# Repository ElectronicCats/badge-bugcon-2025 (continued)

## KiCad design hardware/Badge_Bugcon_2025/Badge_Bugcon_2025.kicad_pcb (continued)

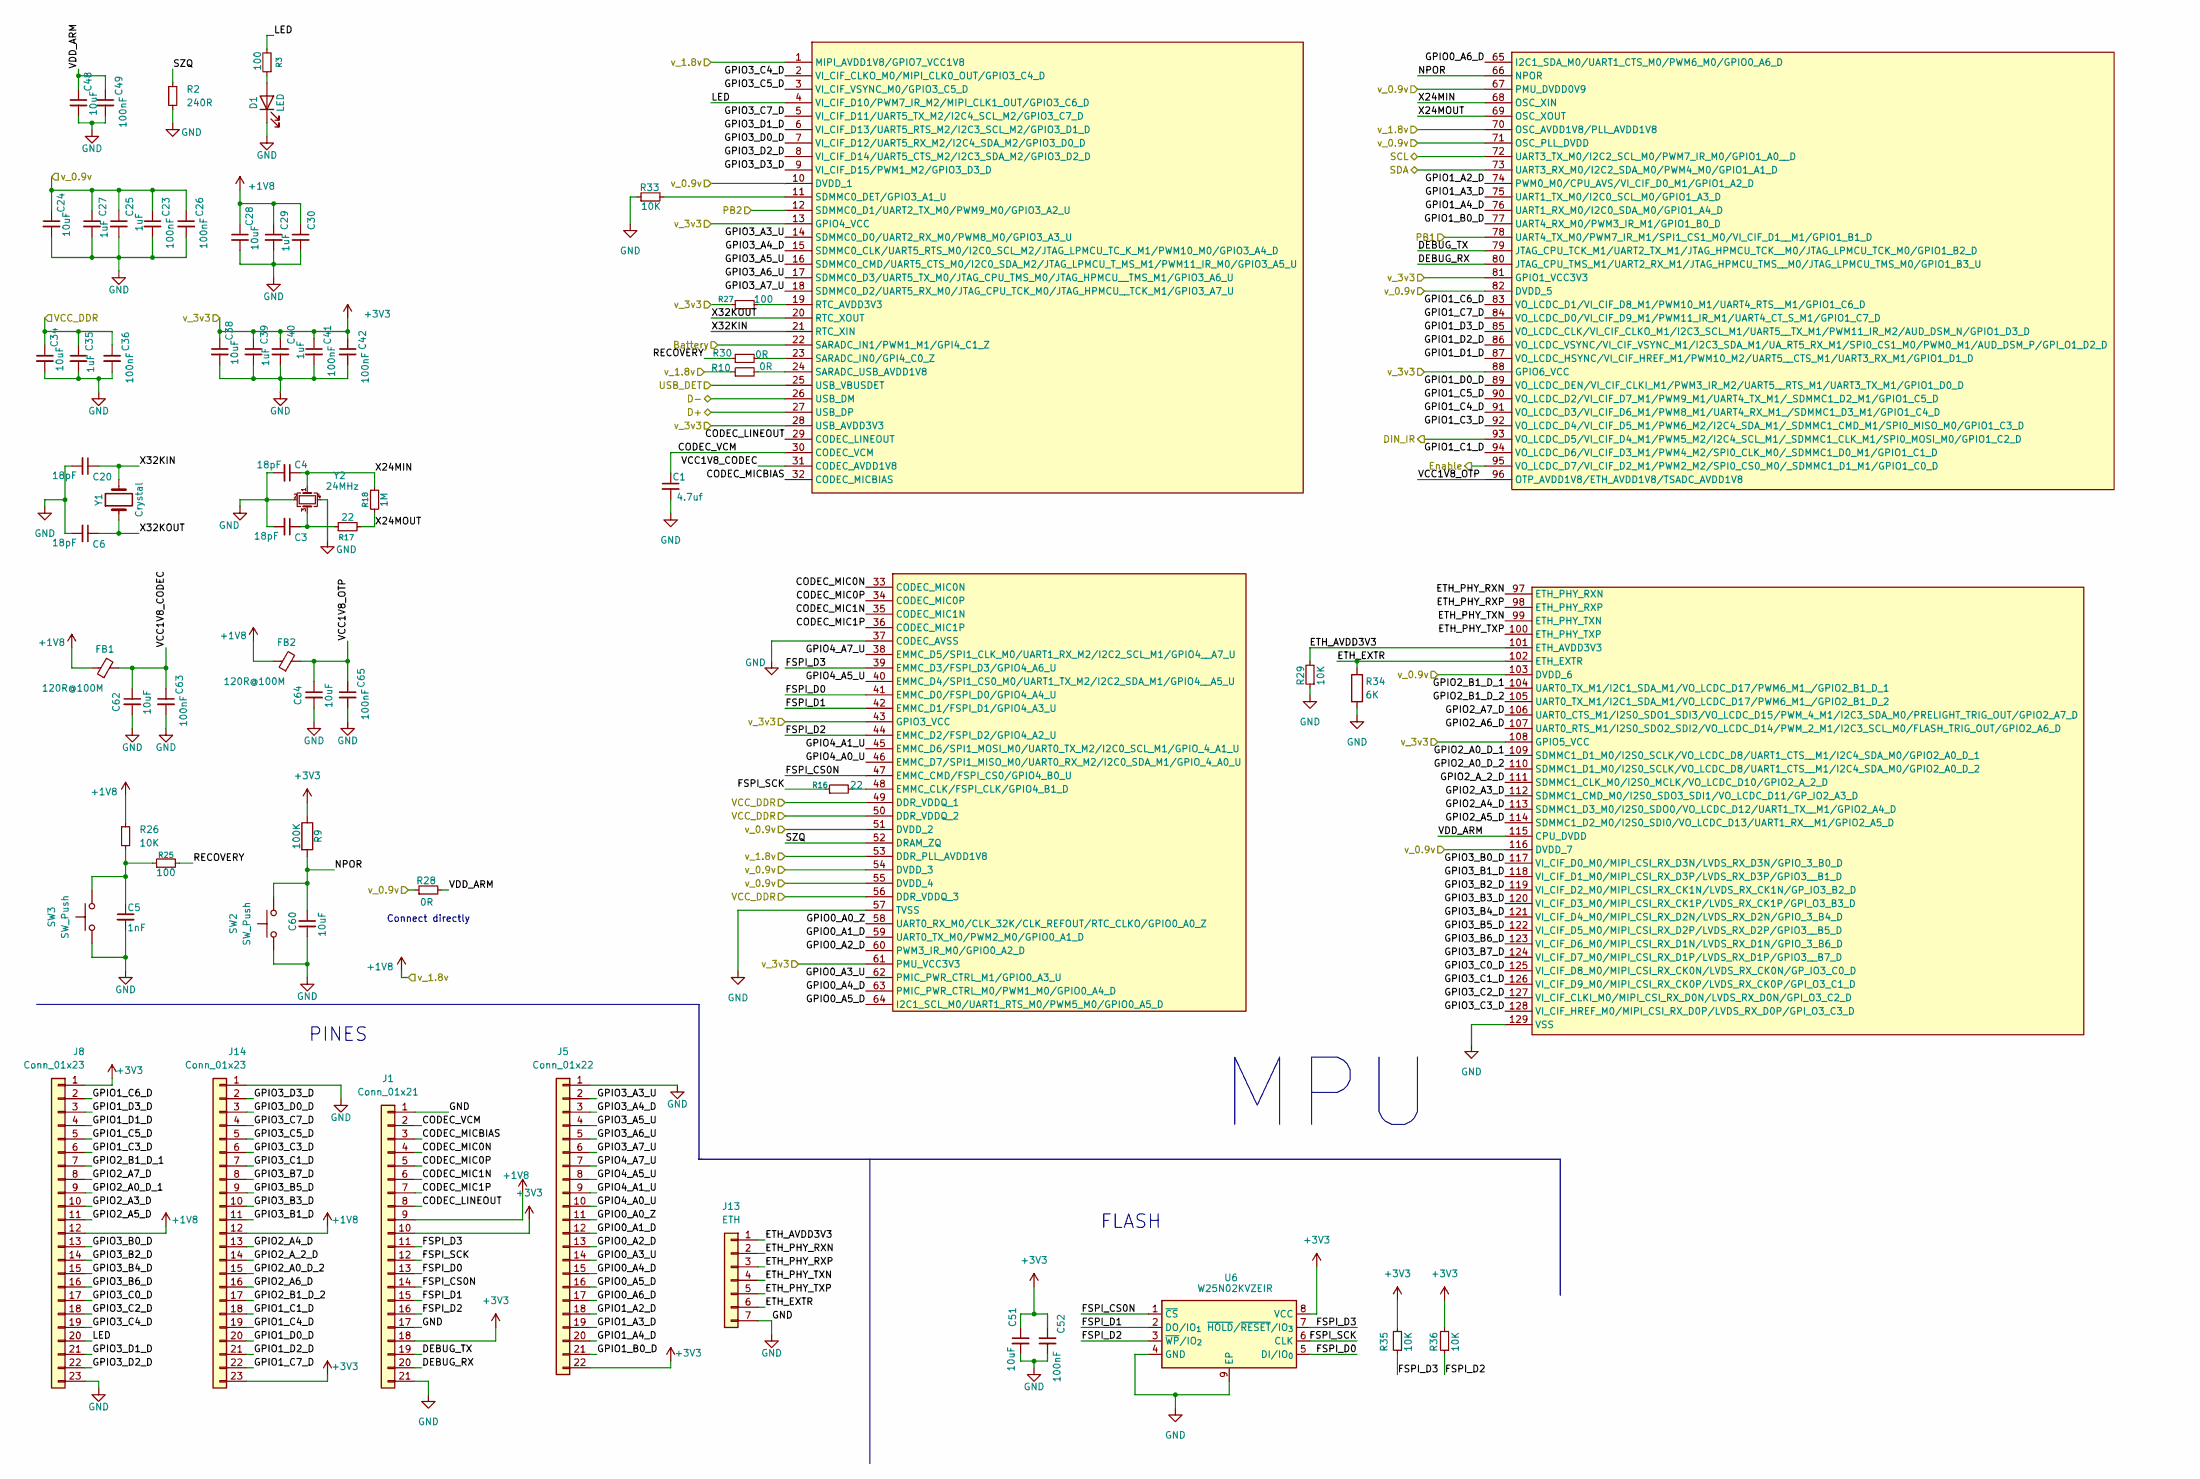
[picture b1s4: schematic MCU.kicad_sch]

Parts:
C1: 4.7uf; C_0402_1005Metric; LCSC# C6119795
C3, C4, C6, C20: 18pF; C_0402_1005Metric; LCSC# C161534
C5: 1nF; C_0402_1005Metric; LCSC# C189467
C23, C26, C36, C41, C42, C49, C52, C63, C65: 100nF; C_0402_1005Metric; LCSC# C77020
C24, C28, C34, C38, C48, C51, C62, C64: 10uF; C_0402_1005Metric; LCSC# C7472949
C25, C27, C29, C30, C35, C39, C40: 1uF; C_0402_1005Metric; LCSC# C52923
C60: 10uF; C_0603_1608Metric; LCSC# C96446
D1: LED; LED_0603_1608Metric; LCSC# C375573
FB1, FB2: 120R@100M; L_0603_1608Metric; LCSC# C14709
J1: Conn_01x21; PinHeader_1x21_P2.54mm_Vertical
J5: Conn_01x22; PinHeader_1x22_P2.54mm_Vertical
J8, J14: Conn_01x23; PinHeader_1x23_P2.54mm_Vertical
J13: ETH; PinHeader_1x07_P2.54mm_Vertical
R2: 240R; R_0402_1005Metric; LCSC# C25094
R3, R25, R27: 100; R_0402_1005Metric; LCSC# C2906860
R9: 100K; R_0402_1005Metric; LCSC# C844674
R10, R28, R30: 0R; R_0402_1005Metric; LCSC# C106231
R16, R17: 22; R_0402_1005Metric; LCSC# C159964
R18: 1M; R_0402_1005Metric; LCSC# C131492
R26, R29, R33, R35, R36: 10K; R_0402_1005Metric; LCSC# C2759535
R34: 6K; R_0805_2012Metric; LCSC# C2828725
SW2, SW3: SW_Push; TS1088R02026; LCSC# C455281
U6: W25N02KVZEIR; WSON-8-1EP_8x6mm_P1.27mm_EP3.4x4.3mm; LCSC# C3010298
U8: RV1106G3; LCSC# C5328706
Y1: Crystal; Crystal_SMD_3215-2Pin_3.2x1.5mm; LCSC# C620155
Y2: 24MHz; Crystal_SMD_3225-4Pin_3.2x2.5mm; LCSC# C70590

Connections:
+1V8: C28.1, C29.1, C30.1, FB1.1, FB2.1, J1.9, J8.12, J14.12, R10.1, R26.1, U8.1 (MIPI_AVDD1V8/GPIO7_VCC1V8), U8.53 (DDR_PLL_AVDD1V8), U8.70 (OSC_AVDD1V8/PLL_AVDD1V8); also elsewhere on the board
+3V3: C38.1, C39.1, C40.1, C41.1, C42.1, C51.1, C52.1, J1.10, J1.18, J5.22, J8.1, J14.23, R9.1, R27.1, R35.2, R36.2, U6.8 (VCC), U8.13 (GPIO4_VCC), U8.28 (USB_AVDD3V3), U8.43 (GPIO3_VCC), U8.61 (PMU_VCC3V3), U8.81 (GPIO1_VCC3V3), U8.88 (GPIO6_VCC), U8.108 (GPIO5_VCC); also elsewhere on the board
/Buck_Converter/VCC_DDR: C34.1, C35.1, C36.1, U8.49 (DDR_VDDQ_1), U8.50 (DDR_VDDQ_2), U8.56 (DDR_VDDQ_3); also elsewhere on the board
/Buck_Converter/v_0.9v: C23.1, C24.1, C25.1, C26.1, C27.1, R28.1, U8.10 (DVDD_1), U8.51 (DVDD_2), U8.54 (DVDD_3), U8.55 (DVDD_4), U8.67 (PMU_DVDD0V9), U8.71 (OSC_PLL_DVDD), U8.82 (DVDD_5), U8.103 (DVDD_6), U8.116 (DVDD_7); also elsewhere on the board
/MCU/Battery: U8.22 (SARADC_IN1/PWM1_M1/GPI4_C1_Z); also elsewhere on the board
/MCU/CODEC_LINEOUT: J1.8, U8.29 (CODEC_LINEOUT)
/MCU/CODEC_MIC0N: J1.4, U8.33 (CODEC_MIC0N)
/MCU/CODEC_MIC0P: J1.5, U8.34 (CODEC_MIC0P)
/MCU/CODEC_MIC1N: J1.6, U8.35 (CODEC_MIC1N)
/MCU/CODEC_MIC1P: J1.7, U8.36 (CODEC_MIC1P)
/MCU/CODEC_MICBIAS: J1.3, U8.32 (CODEC_MICBIAS)
/MCU/CODEC_VCM: C1.1, J1.2, U8.30 (CODEC_VCM)
/MCU/D+: U8.27 (USB_DP); also elsewhere on the board
/MCU/D-: U8.26 (USB_DM); also elsewhere on the board
/MCU/DEBUG_RX: J1.20, U8.80 (JTAG_CPU_TMS_M1/UART2_RX_M1/JTAG_HPMCU_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)
/MCU/DEBUG_TX: J1.19, U8.79 (JTAG_CPU_TCK_M1/UART2_TX_M1/JTAG_HPMCU_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)
/MCU/DIN_IR: U8.93 (VO_LCDC_D5/VI_CIF_D4_M1/PWM5_M2/I2C4_SC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); also elsewhere on the board
/MCU/ETH_AVDD3V3: J13.1, R29.2, U8.101 (ETH_AVDD3V3)
/MCU/ETH_EXTR: J13.6, R34.1, U8.102 (ETH_EXTR)
/MCU/ETH_PHY_RXN: J13.2, U8.97 (ETH_PHY_RXN)
/MCU/ETH_PHY_RXP: J13.3, U8.98 (ETH_PHY_RXP)
/MCU/ETH_PHY_TXN: J13.4, U8.99 (ETH_PHY_TXN)
/MCU/ETH_PHY_TXP: J13.5, U8.100 (ETH_PHY_TXP)
/MCU/Enable: U8.95 (VO_LCDC_D7/VI_CIF_D2_M1/PWM2_M2/SPI0_CS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); also elsewhere on the board
/MCU/FSPI_CS0N: J1.14, U6.1 (~CS), U8.47 (EMMC_CMD/FSPI_CS0/GPIO4_B0_U)
/MCU/FSPI_D0: J1.13, U6.5 (DI/IO_{0}), U8.41 (EMMC_D0/FSPI_D0/GPIO4_A4_U)
/MCU/FSPI_D1: J1.15, U6.2 (DO/IO_{1}), U8.42 (EMMC_D1/FSPI_D1/GPIO4_A3_U)
/MCU/FSPI_D2: J1.16, R36.1, U6.3 (~WP/IO_{2}), U8.44 (EMMC_D2/FSPI_D2/GPIO4_A2_U)
/MCU/FSPI_D3: J1.11, R35.1, U6.7 (~HOLD/~RESET/IO_{3}), U8.39 (EMMC_D3/FSPI_D3/GPIO4_A6_U)
/MCU/FSPI_SCK: J1.12, R16.1, U6.6 (CLK)
/MCU/GPIO0_A0_Z: J5.11, U8.58 (UART0_RX_M0/CLK_32K/CLK_REFOUT/RTC_CLKO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)
/MCU/GPIO0_A1_D: J5.12, U8.59 (UART0_TX_M0/PWM2_M0/GPIO0_A1_D)
/MCU/GPIO0_A2_D: J5.13, U8.60 (PWM3_IR_M0/GPIO0_A2_D)
/MCU/GPIO0_A3_U: J5.14, U8.62 (PMIC_PWR_CTRL_M1/GPIO0_A3_U)
/MCU/GPIO0_A4_D: J5.15, U8.63 (PMIC_PWR_CTRL_M0/PWM1_M0/GPIO0_A4_D)
/MCU/GPIO0_A5_D: J5.16, U8.64 (I2C1_SCL_M0/UART1_RTS_M0/PWM5_M0/GPIO0_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)
/MCU/GPIO0_A6_D: J5.17, U8.65 (I2C1_SDA_M0/UART1_CTS_M0/PWM6_M0/GPIO0_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)
/MCU/GPIO1_A2_D: J5.18, U8.74 (PWM0_M0/CPU_AVS/VI_CIF_D0_M1/GPIO1_A2_D)
/MCU/GPIO1_A3_D: J5.19, U8.75 (UART1_TX_M0/I2C0_SCL_M0/GPIO1_A3_D)
/MCU/GPIO1_A4_D: J5.20, U8.76 (UART1_RX_M0/I2C0_SDA_M0/GPIO1_A4_D)
/MCU/GPIO1_B0_D: J5.21, U8.77 (UART4_RX_M0/PWM3_IR_M1/GPIO1_B0_D)
/MCU/GPIO1_C1_D: J14.18, U8.94 (VO_LCDC_D6/VI_CIF_D3_M1/PWM4_M2/SPI0_CL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)
/MCU/GPIO1_C3_D: J8.6, U8.92 (VO_LCDC_D4/VI_CIF_D5_M1/PWM6_M2/I2C4_SD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)
/MCU/GPIO1_C4_D: J14.19, U8.91 (VO_LCDC_D3/VI_CIF_D6_M1/PWM8_M1/UART4_R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)
/MCU/GPIO1_C5_D: J8.5, U8.90 (VO_LCDC_D2/VI_CIF_D7_M1/PWM9_M1/UART4_T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)
/MCU/GPIO1_C6_D: J8.2, U8.83 (VO_LCDC_D1/VI_CIF_D8_M1/PWM10_M1/UART4_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)
/MCU/GPIO1_C7_D: J14.22, U8.84 (VO_LCDC_D0/VI_CIF_D9_M1/PWM11_IR_M1/UAR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)
/MCU/GPIO1_D0_D: J14.20, U8.89 (VO_LCDC_DEN/VI_CIF_CLKI_M1/PWM3_IR_M2/U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)
/MCU/GPIO1_D1_D: J8.4, U8.87 (VO_LCDC_HSYNC/VI_CIF_HREF_M1/PWM10_M2/U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)
/MCU/GPIO1_D2_D: J14.21, U8.86 (VO_LCDC_VSYNC/VI_CIF_VSYNC_M1/I2C3_SDA_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)
/MCU/GPIO1_D3_D: J8.3, U8.85 (VO_LCDC_CLK/VI_CIF_CLKO_M1/I2C3_SCL_M1/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)
/MCU/GPIO2_A0_D_1: J8.9, U8.109 (SDMMC1_D1_M0/I2S0_SCLK/VO_LCDC_D8/UART1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)
/MCU/GPIO2_A0_D_2: J14.15, U8.110 (SDMMC1_D1_M0/I2S0_SCLK/VO_LCDC_D8/UART1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)
/MCU/GPIO2_A3_D: J8.10, U8.112 (SDMMC1_CMD_M0/I2S0_SDO3_SDI1/VO_LCDC_D1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)
/MCU/GPIO2_A4_D: J14.13, U8.113 (SDMMC1_D3_M0/I2S0_SDO0/VO_LCDC_D12/UART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)
/MCU/GPIO2_A5_D: J8.11, U8.114 (SDMMC1_D2_M0/I2S0_SDI0/VO_LCDC_D13/UART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)
/MCU/GPIO2_A6_D: J14.16, U8.107 (UART0_RTS_M1/I2S0_SDO2_SDI2/VO_LCDC_D14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)
/MCU/GPIO2_A7_D: J8.8, U8.106 (UART0_CTS_M1/I2S0_SDO1_SDI3/VO_LCDC_D15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)
/MCU/GPIO2_A_2_D: J14.14, U8.111 (SDMMC1_CLK_M0/I2S0_MCLK/VO_LCDC_D10/GPI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)
/MCU/GPIO2_B1_D_1: J8.7, U8.104 (UART0_TX_M1/I2C1_SDA_M1/VO_LCDC_D17/PWM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)
/MCU/GPIO2_B1_D_2: J14.17, U8.105 (UART0_TX_M1/I2C1_SDA_M1/VO_LCDC_D17/PWM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)
/MCU/GPIO3_A3_U: J5.2, U8.14 (SDMMC0_D0/UART2_RX_M0/PWM8_M0/GPIO3_A3_U)
/MCU/GPIO3_A4_D: J5.3, U8.15 (SDMMC0_CLK/UART5_RTS_M0/I2C0_SCL_M2/JTA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)
/MCU/GPIO3_A5_U: J5.4, U8.16 (SDMMC0_CMD/UART5_CTS_M0/I2C0_SDA_M2/JTA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)
/MCU/GPIO3_A6_U: J5.5, U8.17 (SDMMC0_D3/UART5_TX_M0/JTAG_CPU_TMS_M0/J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)
/MCU/GPIO3_A7_U: J5.6, U8.18 (SDMMC0_D2/UART5_RX_M0/JTAG_CPU_TCK_M0/J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)
/MCU/GPIO3_B0_D: J8.13, U8.117 (VI_CIF_D0_M0/MIPI_CSI_RX_D3N/LVDS_RX_D3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)
/MCU/GPIO3_B1_D: J14.11, U8.118 (VI_CIF_D1_M0/MIPI_CSI_RX_D3P/LVDS_RX_D3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)
/MCU/GPIO3_B2_D: J8.14, U8.119 (VI_CIF_D2_M0/MIPI_CSI_RX_CK1N/LVDS_RX_C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)
/MCU/GPIO3_B3_D: J14.10, U8.120 (VI_CIF_D3_M0/MIPI_CSI_RX_CK1P/LVDS_RX_C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)
/MCU/GPIO3_B4_D: J8.15, U8.121 (VI_CIF_D4_M0/MIPI_CSI_RX_D2N/LVDS_RX_D2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)
/MCU/GPIO3_B5_D: J14.9, U8.122 (VI_CIF_D5_M0/MIPI_CSI_RX_D2P/LVDS_RX_D2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)
/MCU/GPIO3_B6_D: J8.16, U8.123 (VI_CIF_D6_M0/MIPI_CSI_RX_D1N/LVDS_RX_D1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)
/MCU/GPIO3_B7_D: J14.8, U8.124 (VI_CIF_D7_M0/MIPI_CSI_RX_D1P/LVDS_RX_D1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)
/MCU/GPIO3_C0_D: J8.17, U8.125 (VI_CIF_D8_M0/MIPI_CSI_RX_CK0N/LVDS_RX_C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)
/MCU/GPIO3_C1_D: J14.7, U8.126 (VI_CIF_D9_M0/MIPI_CSI_RX_CK0P/LVDS_RX_C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)
/MCU/GPIO3_C2_D: J8.18, U8.127 (VI_CIF_CLKI_M0/MIPI_CSI_RX_D0N/LVDS_RX_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)
/MCU/GPIO3_C3_D: J14.6, U8.128 (VI_CIF_HREF_M0/MIPI_CSI_RX_D0P/LVDS_RX_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)
/MCU/GPIO3_C4_D: J8.19, U8.2 (VI_CIF_CLKO_M0/MIPI_CLK0_OUT/GPIO3_C4_D)
/MCU/GPIO3_C5_D: J14.5, U8.3 (VI_CIF_VSYNC_M0/GPIO3_C5_D)
/MCU/GPIO3_C7_D: J14.4, U8.5 (VI_CIF_D11/UART5_TX_M2/I2C4_SCL_M2/GPIO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)
/MCU/GPIO3_D0_D: J14.3, U8.7 (VI_CIF_D12/UART5_RX_M2/I2C4_SDA_M2/GPIO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)
/MCU/GPIO3_D1_D: J8.21, U8.6 (VI_CIF_D13/UART5_RTS_M2/I2C3_SCL_M2/GPI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)
/MCU/GPIO3_D2_D: J8.22, U8.8 (VI_CIF_D14/UART5_CTS_M2/I2C3_SDA_M2/GPI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)
/MCU/GPIO3_D3_D: J14.2, U8.9 (VI_CIF_D15/PWM1_M2/GPIO3_D3_D)
/MCU/GPIO4_A0_U: J5.10, U8.46 (EMMC_D7/SPI1_MISO_M0/UART0_RX_M2/I2C0_S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)
/MCU/GPIO4_A1_U: J5.9, U8.45 (EMMC_D6/SPI1_MOSI_M0/UART0_TX_M2/I2C0_S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)
/MCU/GPIO4_A5_U: J5.8, U8.40 (EMMC_D4/SPI1_CS0_M0/UART1_TX_M2/I2C2_SD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)
/MCU/GPIO4_A7_U: J5.7, U8.38 (EMMC_D5/SPI1_CLK_M0/UART1_RX_M2/I2C2_SC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)
/MCU/LED: J8.20, R3.2, U8.4 (VI_CIF_D10/PWM7_IR_M2/MIPI_CLK1_OUT/GPI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)
/MCU/NPOR: C60.1, R9.2, SW2.2, U8.66 (NPOR)
/MCU/PB1: U8.78 (UART4_TX_M0/PWM7_IR_M1/SPI1_CS1_M0/VI_C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); also elsewhere on the board
/MCU/PB2: U8.12 (SDMMC0_D1/UART2_TX_M0/PWM9_M0/GPIO3_A2_U); also elsewhere on the board
/MCU/RECOVERY: R25.2, R30.1
/MCU/SCL: U8.72 (UART3_TX_M0/I2C2_SCL_M0/PWM7_IR_M0/GPIO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); also elsewhere on the board
/MCU/SDA: U8.73 (UART3_RX_M0/I2C2_SDA_M0/PWM4_M0/GPIO1_A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); also elsewhere on the board
/MCU/SZQ: R2.1, U8.52 (DRAM_ZQ)
/MCU/USB_DET: U8.25 (USB_VBUSDET); also elsewhere on the board
/MCU/VCC1V8_CODEC: C62.1, C63.1, FB1.2, U8.31 (CODEC_AVDD1V8)
/MCU/VCC1V8_OTP: C64.1, C65.1, FB2.2, U8.96 (OTP_AVDD1V8/ETH_AVDD1V8/TSADC_AVDD1V8)
/MCU/VDD_ARM: C48.1, C49.1, R28.2, U8.115 (CPU_DVDD)
/MCU/X24MIN: C4.1, R18.1, U8.68 (OSC_XIN), Y2.1
/MCU/X24MOUT: R17.2, R18.2, U8.69 (OSC_XOUT)
/MCU/X32KIN: C20.1, U8.21 (RTC_XIN), Y1.2
/MCU/X32KOUT: C6.1, U8.20 (RTC_XOUT), Y1.1
GND: C1.2, C3.2, C4.2, C5.2, C6.2, C20.2, C23.2, C24.2, C25.2, C26.2, C27.2, C28.2, C29.2, C30.2, C34.2, C35.2, C36.2, C38.2, C39.2, C40.2, C41.2, C42.2, C48.2, C49.2, C51.2, C52.2, C60.2, C62.2, C63.2, C64.2, C65.2, D1.1 (K), J1.1, J1.17, J1.21, J5.1, J8.23, J13.7, J14.1, R2.2, R29.1, R33.1, R34.2, SW2.1, SW3.1, U6.4 (GND), U6.9 (EP), U8.37 (CODEC_AVSS), U8.57 (TVSS), U8.129 (VSS), Y2.2, Y2.4; also elsewhere on the board
unnamed: C3.1, R17.1, Y2.3
unnamed: C5.1, R25.1, R26.2, SW3.2
unnamed: D1.2 (A), R3.1
unnamed: R27.2, U8.19 (RTC_AVDD3V3)
unnamed: R30.2, U8.23 (SARADC_IN0/GPI4_C0_Z)
unnamed: R10.2, U8.24 (SARADC_USB_AVDD1V8)
unnamed: R33.2, U8.11 (SDMMC0_DET/GPIO3_A1_U)
unnamed: R16.2, U8.48 (EMMC_CLK/FSPI_CLK/GPIO4_B1_D)

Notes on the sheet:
MPU
Connect directly
PINES
FLASH

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
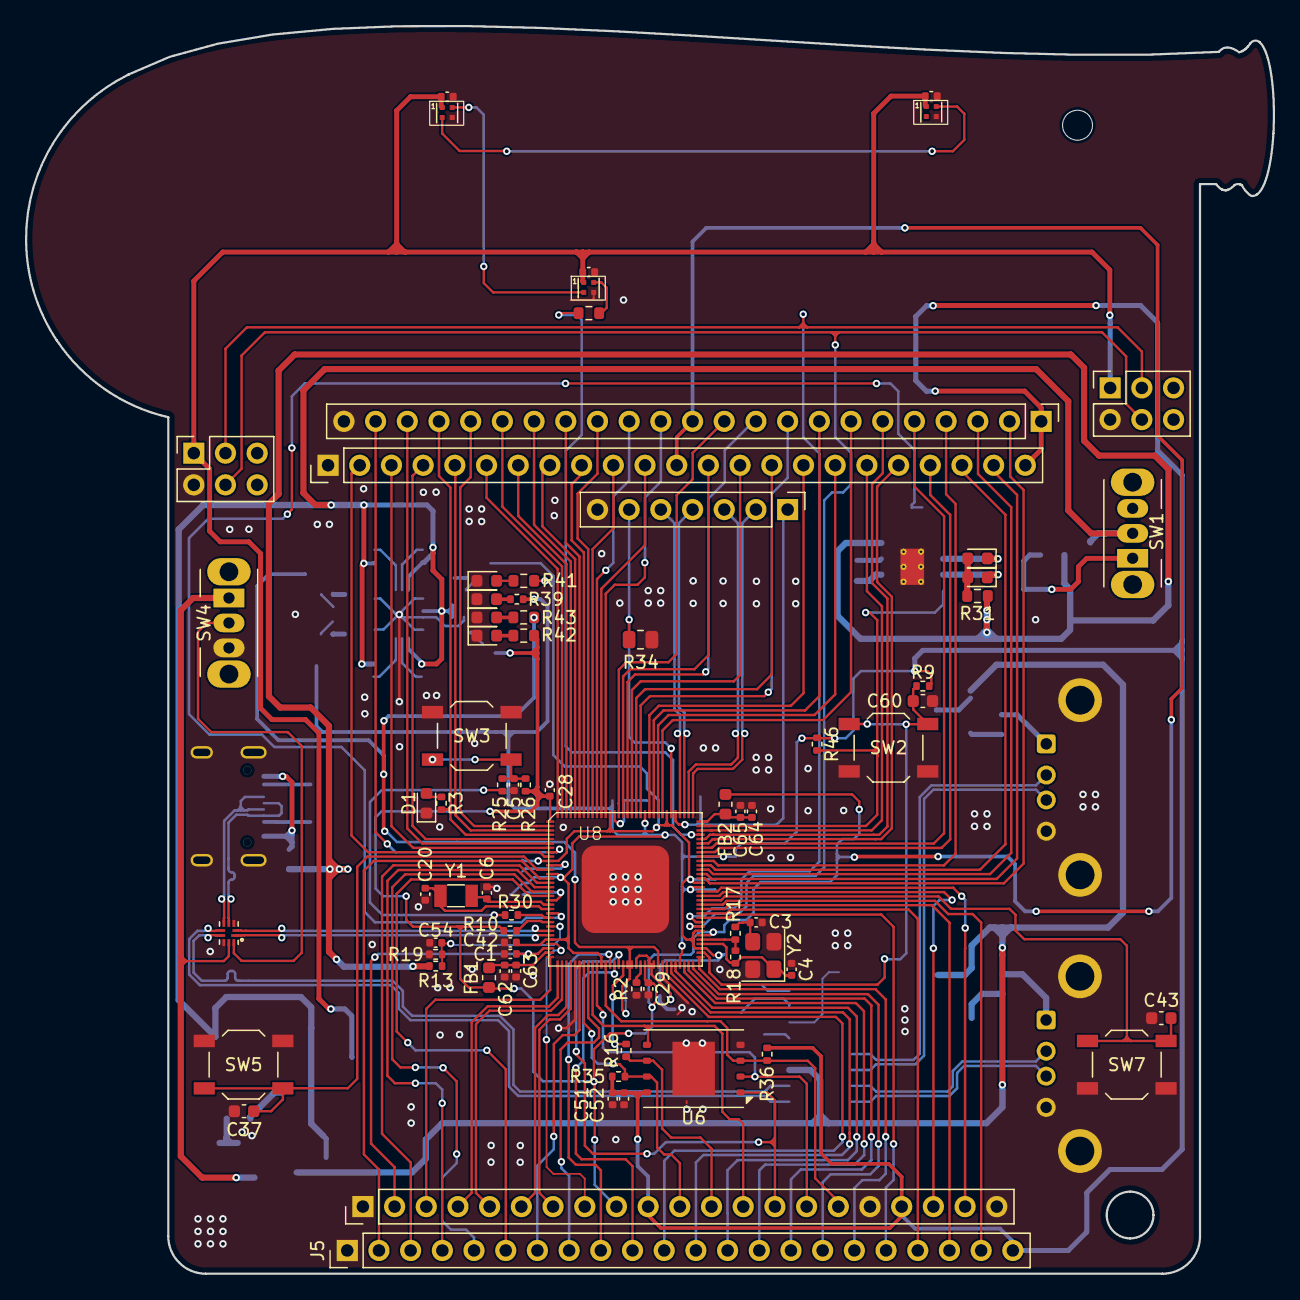
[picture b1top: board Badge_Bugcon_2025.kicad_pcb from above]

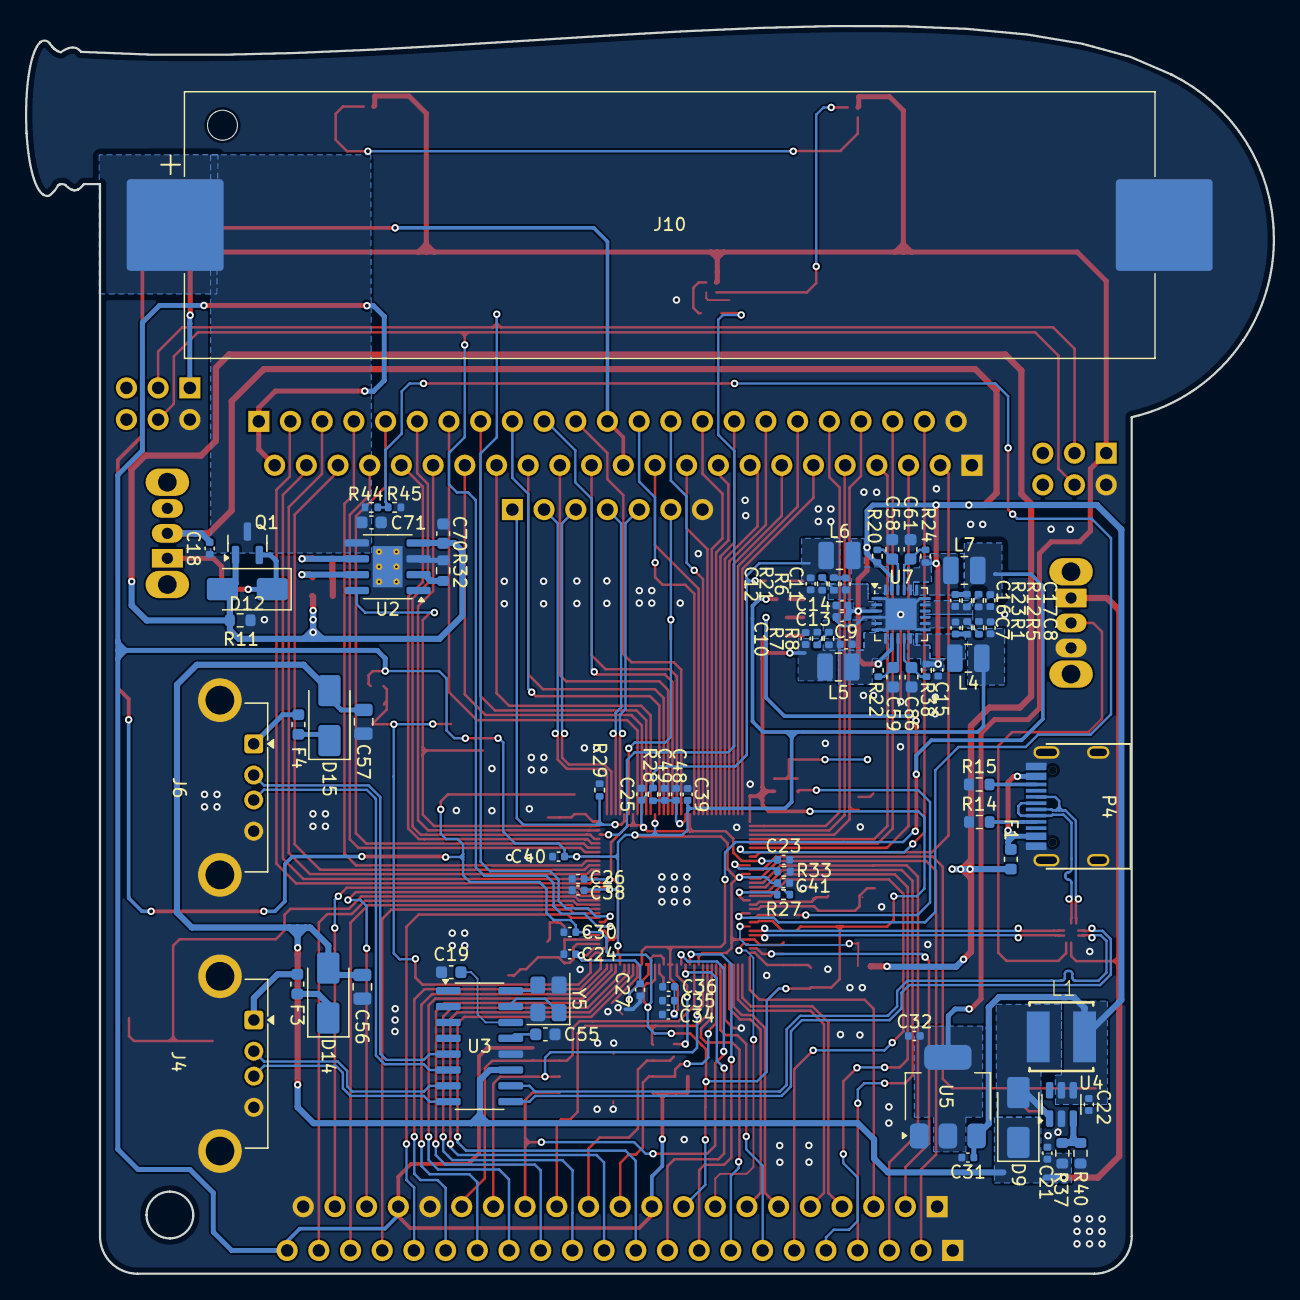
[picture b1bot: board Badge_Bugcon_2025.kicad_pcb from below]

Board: 2 copper layers, 100.0 x 100.0 mm, 162 parts (88 on the bottom side), 165 nets.

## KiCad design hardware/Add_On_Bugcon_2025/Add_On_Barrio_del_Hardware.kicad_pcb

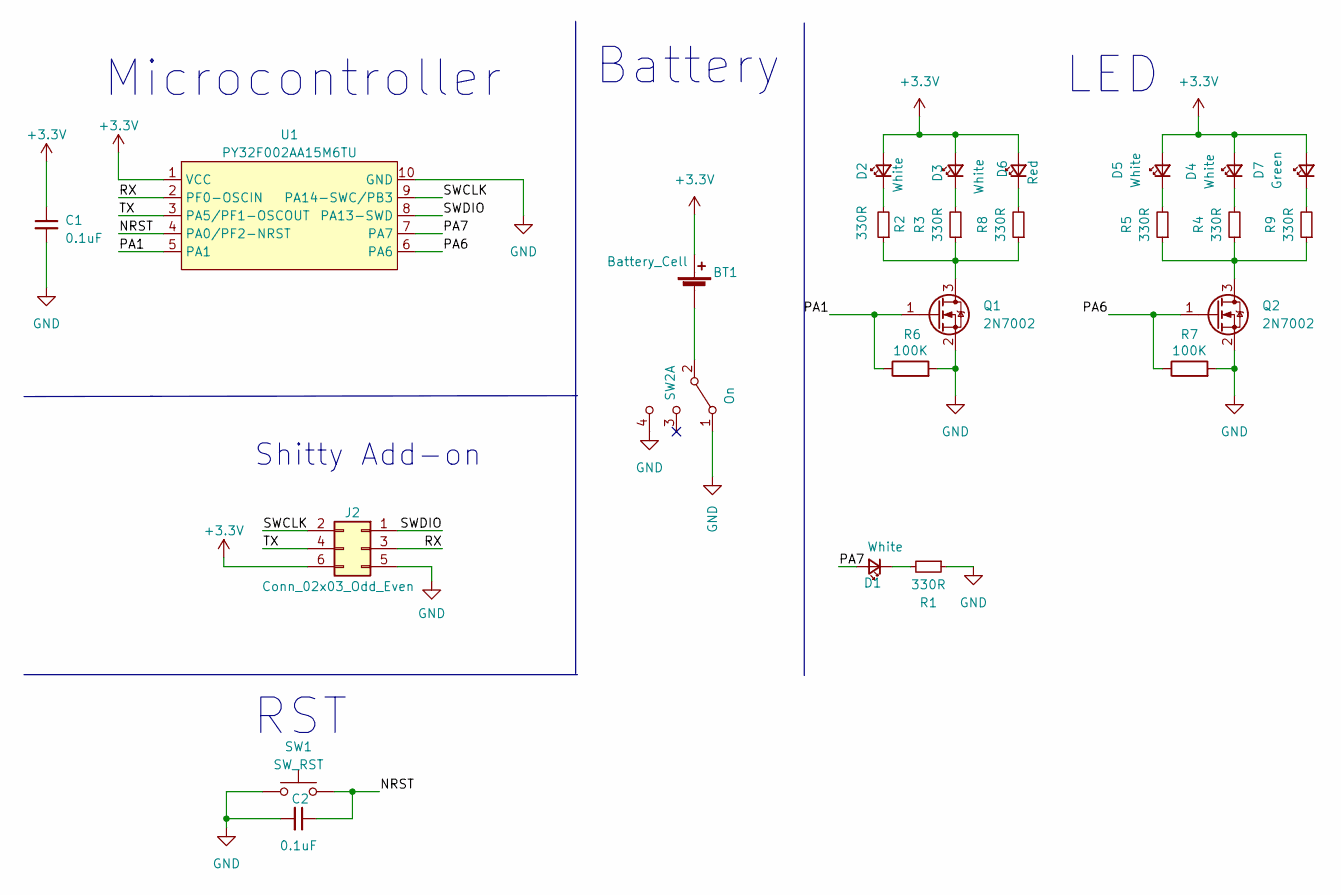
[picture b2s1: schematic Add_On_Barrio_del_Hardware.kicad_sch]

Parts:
BT1: Battery_Cell; BAT-HLD-001; LCSC# C964833
C1, C2: 0.1uF; C_0805_2012Metric; LCSC# C282732
D1: White; LED_0603_1608Metric; LCSC# C2290
D2, D3, D4, D5: White; LYT77K-K2M1-NoHole
D6: Red; LED_0603_1608Metric; LCSC# C2286
D7: Green; LED_0603_1608Metric; LCSC# C916074
J2: Conn_02x03_Odd_Even; PinHeader_2x03_P2.54mm_Vertical_SMD; LCSC# C780054
Q1, Q2: 2N7002; SOT-23; LCSC# C8545
R1, R2, R3, R4, R5, R8, R9: 330R; R_0603_1608Metric; LCSC# C105881
R6, R7: 100K; R_0805_2012Metric; LCSC# C96346
SW1: SW_RST; SW_SPST_TL3342; LCSC# C318889
SW2: On; MSK12C02; LCSC# C431540
U1: PY32F002AA15M6TU; PY32F002AA15M; LCSC# C5292058

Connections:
+3.3V: BT1.2 (+), C1.1, D2.2 (A), D3.2 (A), D4.2 (A), D5.2 (A), D6.2 (A), D7.2 (A), J2.6, U1.1 (VCC)
/NRST: C2.1, SW1.2, U1.4 (PA0/PF2-NRST)
/PA1: Q1.1 (G), R6.1, U1.5 (PA1)
/PA6: Q2.1 (G), R7.1, U1.6 (PA6)
/PA7: D1.2 (A), U1.7 (PA7)
/RX: J2.3, U1.2 (PF0-OSCIN)
/SWCLK: J2.2, U1.9 (PA14-SWC/PB3)
/SWDIO: J2.1, U1.8 (PA13-SWD)
/TX: J2.4, U1.3 (PA5/PF1-OSCOUT)
GND: C1.2, C2.2, J2.5, Q1.2 (S), Q2.2 (S), R1.1, R6.2, R7.2, SW1.1, SW2.1 (A), SW2.4 (C), U1.10 (GND)
unnamed: BT1.1 (-), SW2.2 (B)
unnamed: D1.1 (K), R1.2
unnamed: D2.1 (K), R2.2
unnamed: D3.1 (K), R3.2
unnamed: D4.1 (K), R4.2
unnamed: D5.1 (K), R5.2
unnamed: D6.1 (K), R8.2
unnamed: D7.1 (K), R9.2
unnamed: Q1.3 (D), R2.1, R3.1, R8.1
unnamed: Q2.3 (D), R4.1, R5.1, R9.1

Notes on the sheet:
LED
Shitty Add-on
RST
Microcontroller
Battery

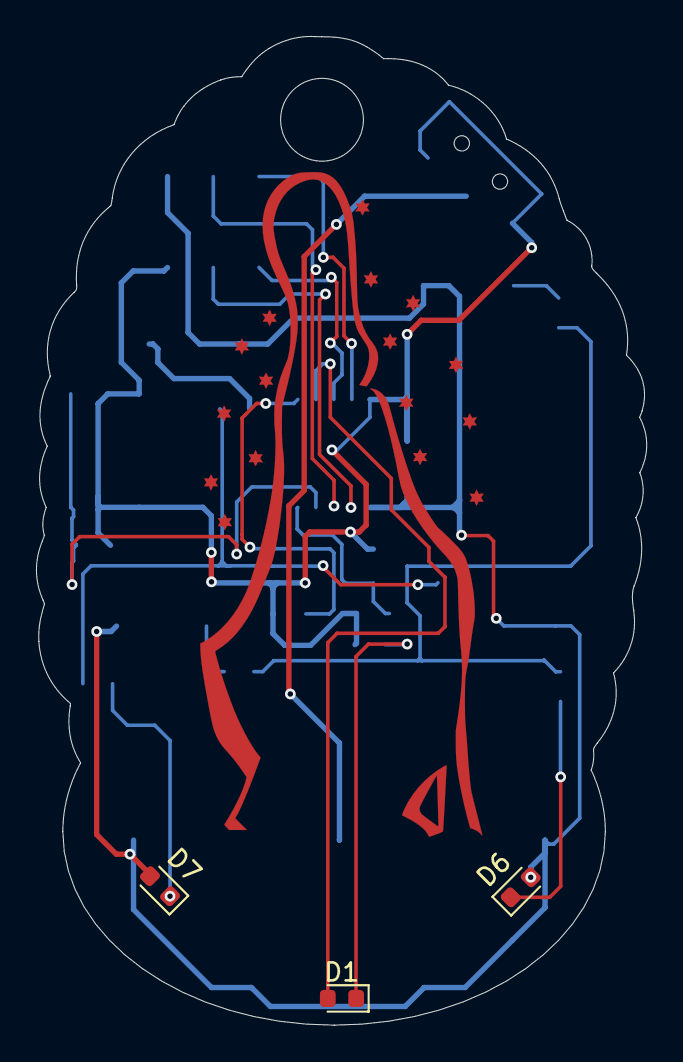
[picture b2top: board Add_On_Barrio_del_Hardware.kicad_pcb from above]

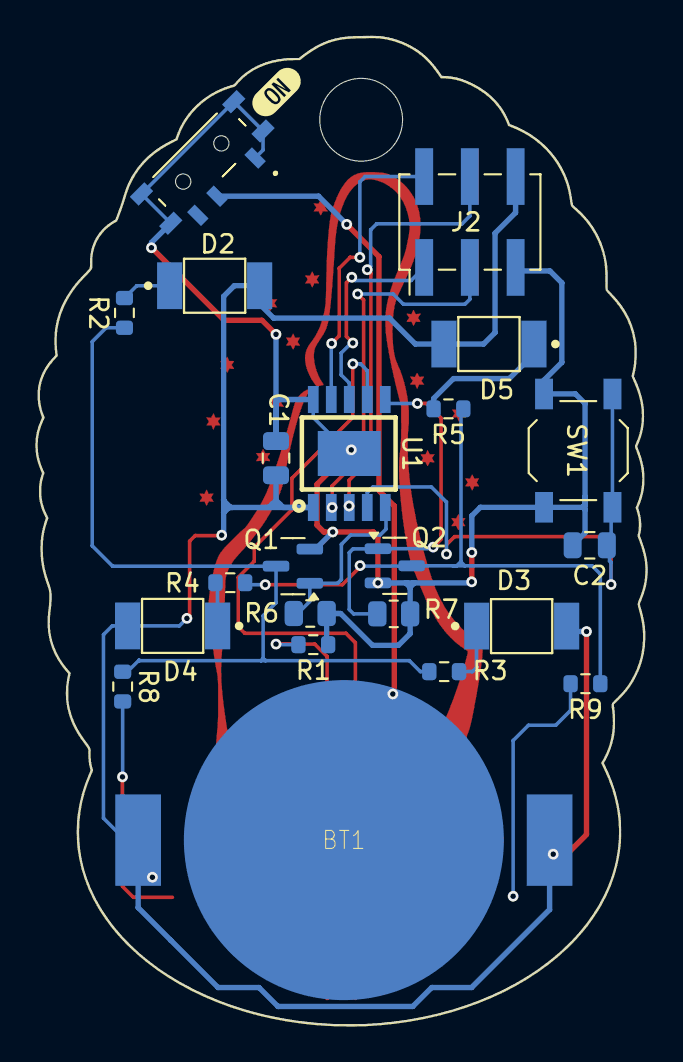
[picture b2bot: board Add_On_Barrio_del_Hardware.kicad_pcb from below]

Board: 2 copper layers, 33.9 x 54.9 mm, 27 parts (23 on the bottom side), 20 nets.

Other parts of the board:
Ref**: Val**; VIRGEN DE GUADALUPE
kibuzzard-68DB0924: G***; kibuzzard-68DB0924

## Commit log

2025-09-17 feat(Hw):Init_Schematic
2025-09-18 feat(Hw):Update_Schematic
2025-09-24 feat(Hw):Add_On_File_Added
2025-09-24 feat(Hw):Update_files
2025-09-24 feat(Hw):Add_On_Kicad_File_Added
2025-09-25 feat(HW):Init_Sch_PCB
2025-09-26 feat(Hw):Update_And_Route_PCB
2025-09-26 feat(Hw):Update_BOM
2025-09-26 feat(Hw):Init_Floorplan
2025-09-29 feat(Hw):Update_Schematic_And_Floorplan
2025-09-30 feat(Hw)_Update PCB_Hole_Added
2025-09-30 feat(Hw):Wifi_Module_Deleted
2025-10-02 feat(Hw):Update_PCB_Added_Bac_Image
2025-10-09 feat(Hw):Update_Floorplan
2025-10-09 feat(Hw):Updated_Floorplan
2025-10-09 feat(Hw):Init_Route
2025-10-10 feat(Hw):Update_Route
2025-10-14 feat(hw):Updated_review
2025-10-14 feat(Hw):Update_BOM_And_Labels
2025-10-16 feat(Hw):Update_Schaematic_And_BOM
2025-10-17 feat(Hw):Update_Schematic_And_Route
2025-10-20 feat(Hw):Update_Route_And_Schematic
2025-10-21 feat(Hw): Add leds change crytsla routing
2025-10-21 feat(Hw):Update_USB_Selector
2025-10-21 update connections same image layer
2025-10-22 fix(hw): route pads
2025-11-04 docs: update README
2025-11-14 feat(Fw):Firmware_Add_On_Added
2025-11-21 docs: Add SDK link to README.md
2025-11-21 docs: Add 'Blink Blink!' section to README
    Added a new section for 'Blink Blink!' instructions.
2025-11-21 Revise README with updated specs and instructions
    Updated technical specifications and instructions for the Bugcon 2025 badge, including hardware details and flashing instructions for Windows and macOS.
2025-11-24 docs: Add access information to README
    Added access credentials for the device.
